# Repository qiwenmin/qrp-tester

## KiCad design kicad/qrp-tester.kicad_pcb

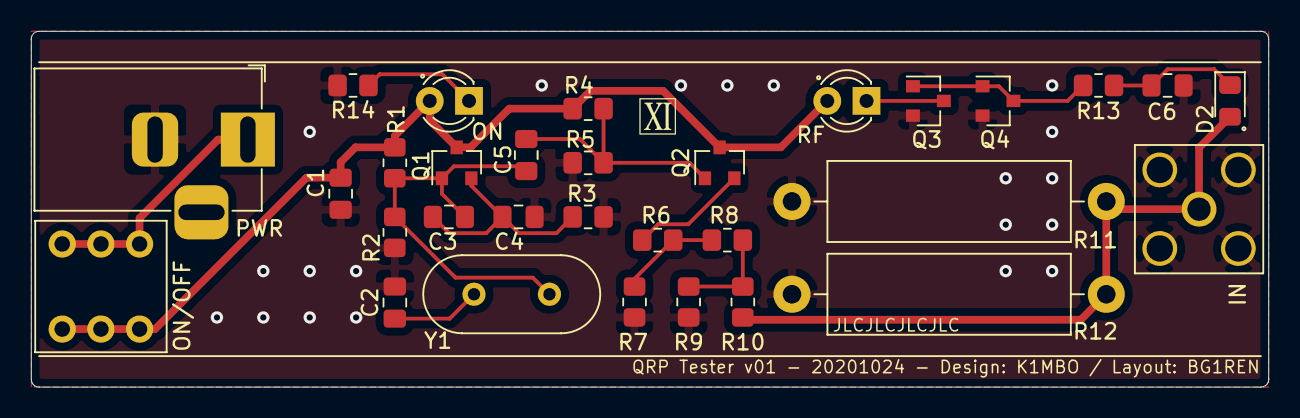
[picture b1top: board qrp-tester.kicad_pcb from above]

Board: 2 copper layers, 80.0 x 23.0 mm, 31 parts (0 on the bottom side), 15 nets.

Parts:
C1, C2: 0.1u; C_0805_2012Metric_Pad1.18x1.45mm_HandSolder
C3, C4: 1n; C_0805_2012Metric_Pad1.18x1.45mm_HandSolder
C5: 100p; C_0805_2012Metric_Pad1.18x1.45mm_HandSolder
C6: 10n; C_0805_2012Metric_Pad1.18x1.45mm_HandSolder
D1: RF; LED_D3.0mm
D2: 1N4148; D_0805_2012Metric_Pad1.15x1.40mm_HandSolder
D3: ON; LED_D3.0mm
J1: IN; SMA_Amphenol_132203-12_Horizontal
J2: PWR; BarrelJack_Horizontal
Q1, Q2, Q3, Q4: MMBT3904; SOT-23
R1, R2, R4, R5, R14: 10K; R_0805_2012Metric_Pad1.20x1.40mm_HandSolder
R3, R6, R8, R13: 1K; R_0805_2012Metric_Pad1.20x1.40mm_HandSolder
R7, R9: 33; R_0805_2012Metric_Pad1.20x1.40mm_HandSolder
R10: 330; R_0805_2012Metric_Pad1.20x1.40mm_HandSolder
R11, R12: 100; R_Axial_DIN0516_L15.5mm_D5.0mm_P20.32mm_Horizontal
SW1: ON/OFF; Switch-Push-6pin
Y1: 7023kHz; Crystal_HC49-4H_Vertical

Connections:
GND: C1.2, C2.2, C4.2, C6.2, J1.2, J2.2, Q3.2, Q4.2, R2.2, R3.2, R5.2, R7.2, R9.2, R11.2, R12.2, R14.2
unnamed: C2.1, Y1.2
unnamed: C3.1, C5.2, Q1.1, R1.2, R2.1, Y1.1
unnamed: C3.2, C4.1, Q1.2, R3.1
unnamed: C5.1, Q2.1, R4.2, R5.1
unnamed: C6.1, D2.1, R13.1
unnamed: D1.1, Q3.3
unnamed: D2.2, J1.1, R10.1, R11.1, R12.1
unnamed: D3.1, R14.1
unnamed: J2.1, SW1.2
unnamed: Q2.2, R6.1
unnamed: Q3.1, Q4.1, Q4.3, R13.2
unnamed: R6.2, R7.1, R8.2
unnamed: R8.1, R9.1, R10.2
VCC: C1.1, D1.2, D3.2, Q1.3, Q2.3, R1.1, R4.1, SW1.1

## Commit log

2020-10-23 Initial commit. (v01-20201023)
2020-10-24 Fix a connection bug.
2020-10-28 Adjust for JLC SMT
    - Set the original point at the bottom left in PCB.
    - Add LCSC property for the smd parts.
